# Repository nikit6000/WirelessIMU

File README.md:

# WirelessIMU
A board for wireless motion tracking based on `ESP32-PICO-D4` and `MPU9250`. You also can use `ICM-20948` instead of `MPU9250` but you needs to change LDO at `U1` place to 1.8V one

# Capabilities
* Capture RAW Gyroscope, Accelerometer data to embedded storage
* Control over BLE
* Captured data downloading via Wi-Fi

# Applications
* [iOS Application](https://github.com/tokareva13/WirelessIMU-Control)

# Authors
* [Nikita Tarkhov](https://github.com/nikit6000)
* [Tokareva Irina](https://github.com/tokareva13)

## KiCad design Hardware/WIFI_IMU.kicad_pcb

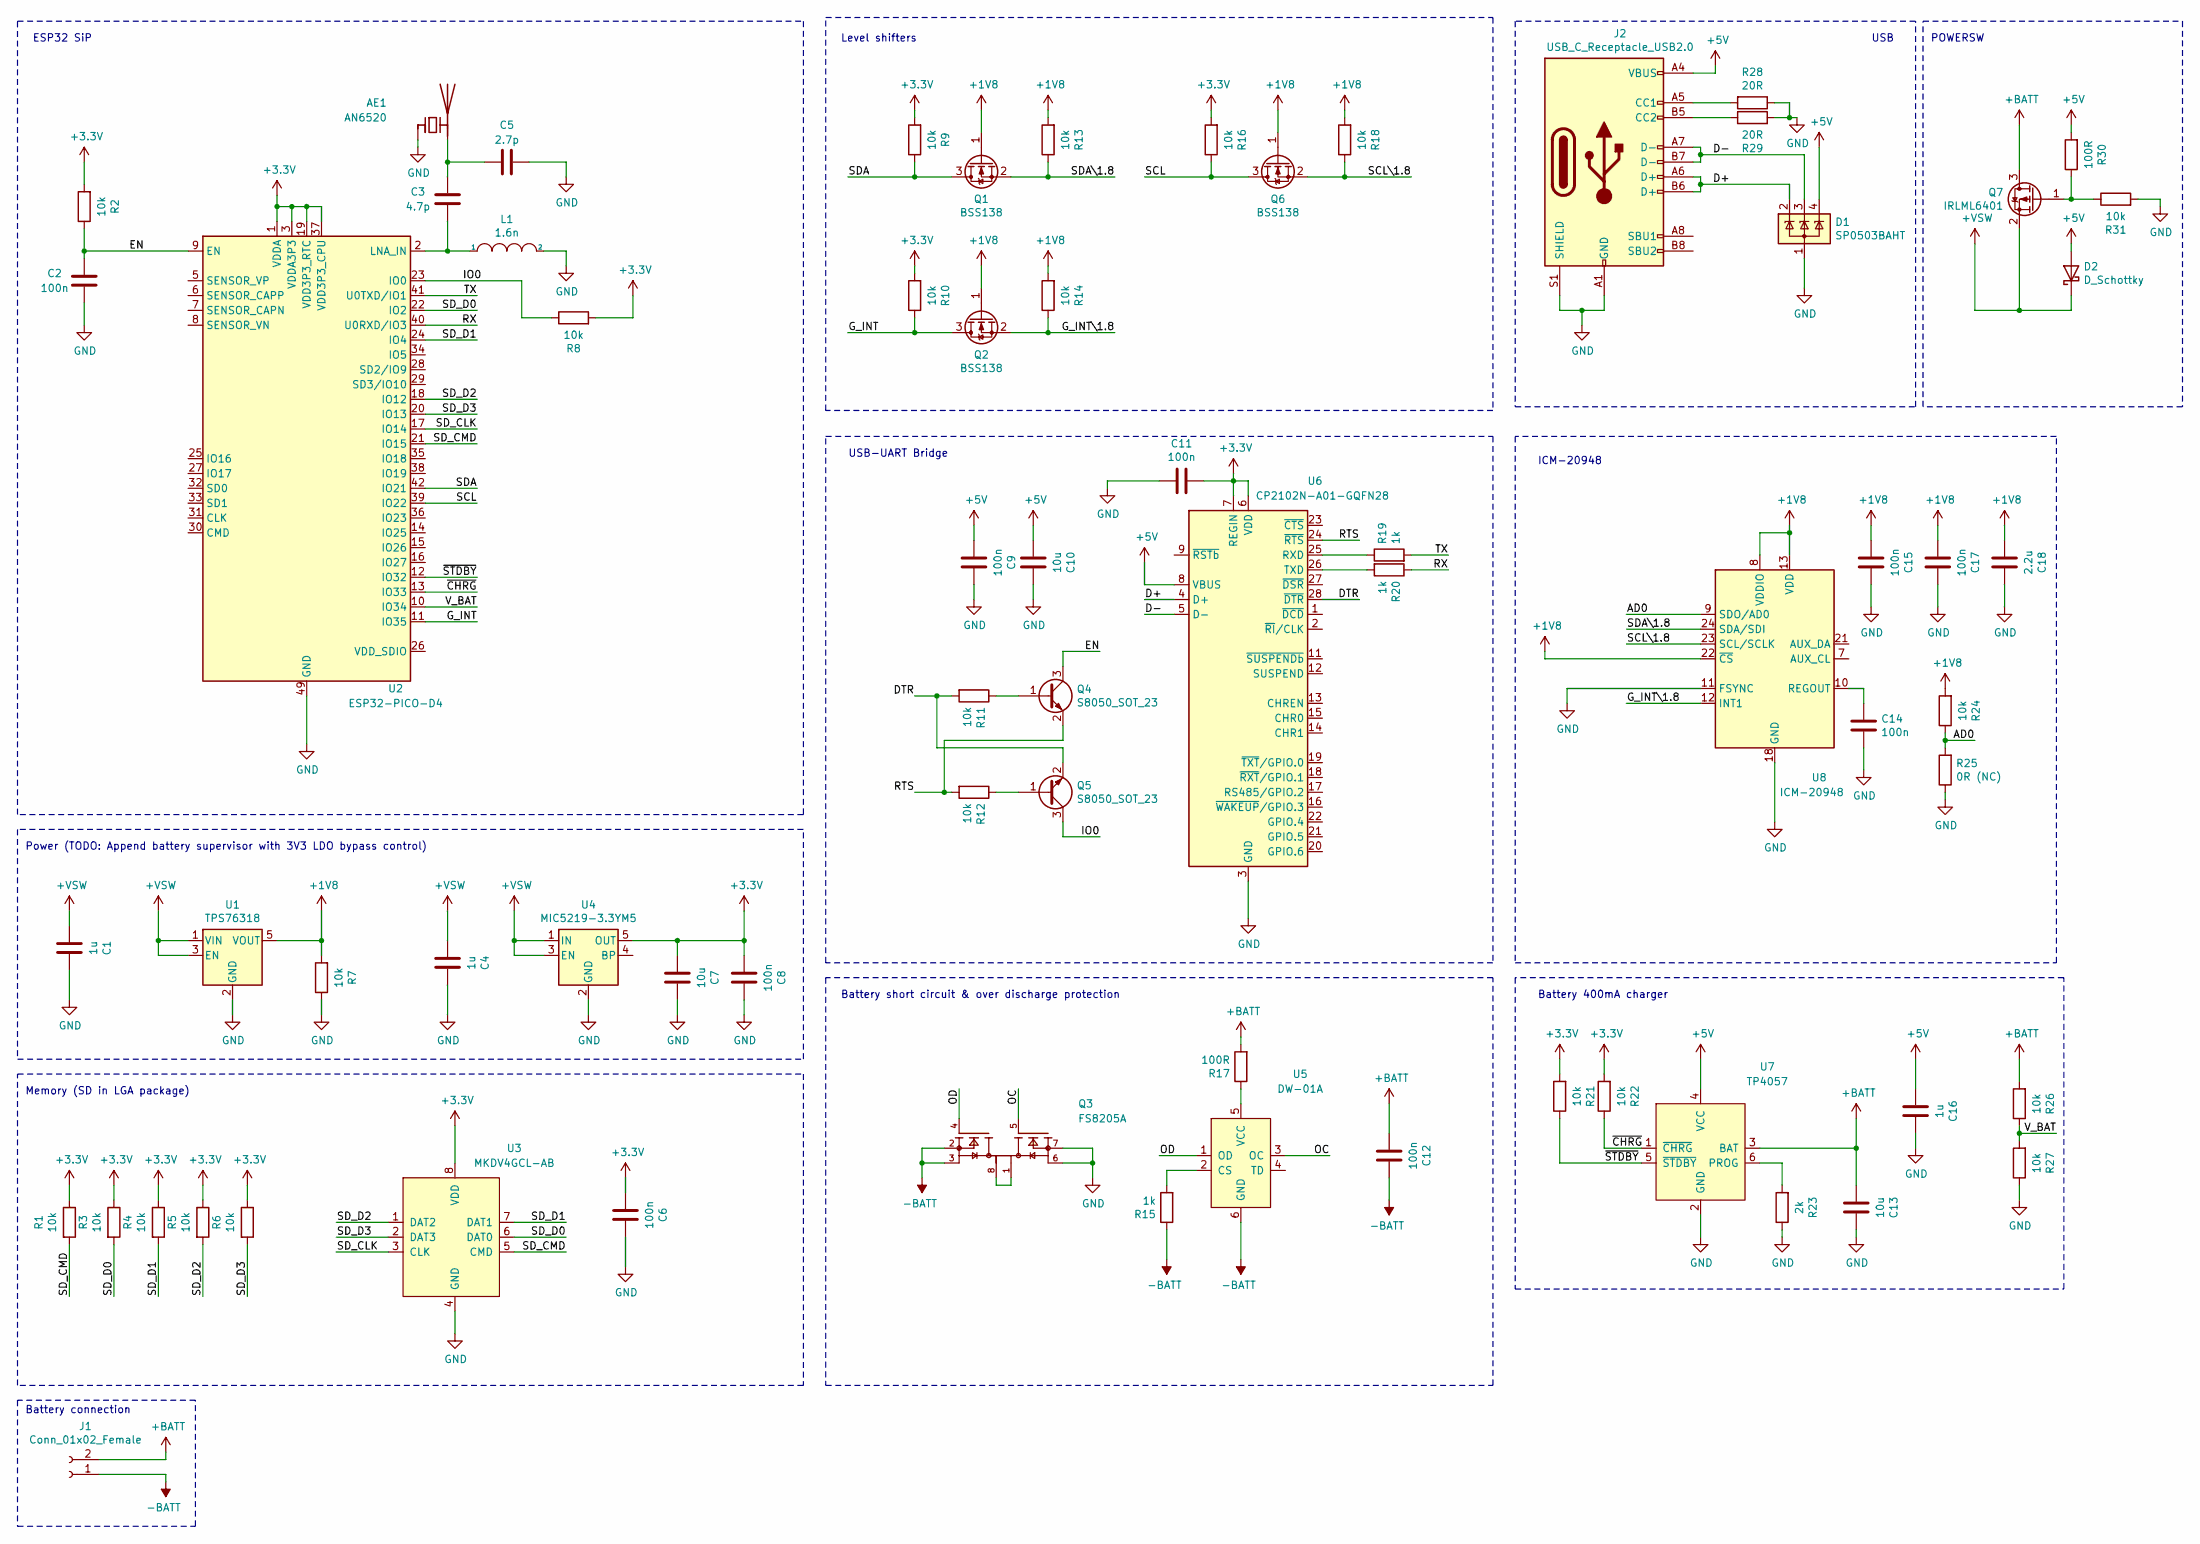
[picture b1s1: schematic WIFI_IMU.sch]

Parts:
AE1: AN6520; CHIP_ANTENNA_AN6520
C1, C4, C16: 1u; C_0402_1005Metric
C2, C6, C8, C9, C11, C12, C14, C15, C17: 100n; C_0402_1005Metric
C3: 4.7p; C_0402_1005Metric
C5: 2.7p; C_0402_1005Metric
C7, C10, C13: 10u; C_0402_1005Metric
C18: 2.2u; C_0402_1005Metric
D1: SP0503BAHT; SOT-143
D2: D_Schottky; D_SOD-323
J1: Conn_01x02_Female; PinHeader_1x02_P1.27mm_Vertical
J2: USB_C_Receptacle_USB2.0; USB_C_Receptacle_HRO_TYPE-C-31-M-12
L1: 1.6n; L_0402_1005Metric
Q1, Q2, Q6: BSS138; SOT-23
Q3: FS8205A; SOP65P640X120-8N; PARTREV 1.7
Q4, Q5: S8050_SOT_23; SOT-23
Q7: IRLML6401; SOT-23
R1, R2, R3, R4, R5, R6, R7, R8, R9, R10, R11, R12, R13, R14, R16, R18, R21, R22, R24, R26, R27, R31: 10k; R_0402_1005Metric
R15, R19, R20: 1k; R_0402_1005Metric
R17, R30: 100R; R_0402_1005Metric
R23: 2k; R_0402_1005Metric
R25: 0R (NC); R_0402_1005Metric
R28, R29: 20R; R_0402_1005Metric
U1: TPS76318; SOT-23-5
U2: ESP32-PICO-D4; QFN-48-1EP_7x7mm_P0.5mm_EP5.3x5.3mm
U3: MKDV4GCL-AB; LGA-8_8x6mm_P1.27
U4: MIC5219-3.3YM5; SOT-23-5
U5: DW-01A; SOT-23-6
U6: CP2102N-A01-GQFN28; QFN-28-1EP_5x5mm_P0.5mm_EP3.35x3.35mm
U7: TP4057; SOT-23-6
U8: ICM-20948; InvenSense_QFN-24_3x3mm_P0.4mm

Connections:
+1V8: C15.2, C17.2, C18.2, Q1.1 (G), Q2.1 (G), Q6.1 (G), R7.2, R13.2, R14.2, R18.2, R24.2, U1.5 (VOUT), U8.8 (VDDIO), U8.13 (VDD), U8.22 (~CS)
+3V3: C6.2, C7.2, C8.2, C11.1, R1.1, R2.2, R3.1, R4.1, R5.1, R6.1, R8.2, R9.2, R10.2, R16.2, R21.2, R22.2, U2.1 (VDDA), U2.3 (VDDA3P3), U2.4 (VDDA3P3), U2.19 (VDD3P3_RTC), U2.37 (VDD3P3_CPU), U2.43 (VDDA), U2.46 (VDDA), U3.8 (VDD), U4.5 (OUT), U6.6 (VDD), U6.7 (REGIN)
+5V: C9.2, C10.2, C16.2, D1.4 (K), D2.2 (A), J2.A4 (VBUS), J2.A9 (VBUS), J2.B4 (VBUS), J2.B9 (VBUS), R30.2, U6.8 (VBUS), U7.4 (VCC)
+BATT: C12.2, C13.2, J1.2, Q7.3 (D), R17.2, R26.2, U7.3 (BAT)
+VSW: C1.2, C4.2, D2.1 (K), Q7.2 (S), U1.1 (VIN), U1.3 (EN), U4.1 (IN), U4.3 (EN)
-BATT: C12.1, J1.1, Q3.2, Q3.3, R15.1, U5.6 (GND)
/AD0: R24.1, R25.2, U8.9 (SDO/AD0)
/D+: D1.2 (K), J2.A6 (D+), J2.B6 (D+), U6.4 (D+)
/D-: D1.3 (K), J2.A7 (D-), J2.B7 (D-), U6.5 (D-)
/DTR: Q5.2 (E), R11.2, U6.28 (~DTR)
/EN: C2.2, Q4.3 (C), R2.1, U2.9 (EN)
/G_INT: Q2.3 (D), R10.1, U2.11 (IO35)
/G_INT\1.8: Q2.2 (S), R14.1, U8.12 (INT1)
/IO0: Q5.3 (C), R8.1, U2.23 (IO0)
/OC: Q3.5, U5.3 (OC)
/OD: Q3.4, U5.1 (OD)
/RTS: Q4.2 (E), R12.2, U6.24 (~RTS)
/RX: R20.1, U2.40 (U0RXD/IO3)
/SCL: Q6.3 (D), R16.1, U2.39 (IO22)
/SCL\1.8: Q6.2 (S), R18.1, U8.23 (SCL/SCLK)
/SDA: Q1.3 (D), R9.1, U2.42 (IO21)
/SDA\1.8: Q1.2 (S), R13.1, U8.24 (SDA/SDI)
/SD_CLK: U2.17 (IO14), U3.3 (CLK)
/SD_CMD: R1.2, U2.21 (IO15), U3.5 (CMD)
/SD_D0: R3.2, U2.22 (IO2), U3.6 (DAT0)
/SD_D1: R4.2, U2.24 (IO4), U3.7 (DAT1)
/SD_D2: R5.2, U2.18 (IO12), U3.1 (DAT2)
/SD_D3: R6.2, U2.20 (IO13), U3.2 (DAT3)
/TX: R19.2, U2.41 (U0TXD/IO1)
/V_BAT: R26.1, R27.2, U2.10 (IO34)
/~CHRG: R22.1, U2.13 (IO33), U7.1 (~CHRG)
/~STDBY: R21.1, U2.12 (IO32), U7.5 (~STDBY)
GND: AE1.2 (FEED), C1.1, C2.1, C4.1, C5.2, C6.1, C7.1, C8.1, C9.1, C10.1, C11.2, C13.1, C14.1, C15.1, C16.1, C17.1, C18.1, D1.1 (A), J2.A1 (GND), J2.A12 (GND), J2.B1 (GND), J2.B12 (GND), J2.S1 (SHIELD), L1.2, Q3.6, Q3.7, R7.1, R23.1, R25.1, R27.1, R28.1, R29.2, R31.2, U1.2 (GND), U2.49 (GND), U3.4 (GND), U4.2 (GND), U6.3 (GND), U6.29 (GND), U7.2 (GND), U8.11 (FSYNC), U8.18 (GND), U8.20 (GND)
unnamed: AE1.1 (PCB_Trace), C3.2, C5.1
unnamed: C3.1, L1.1, U2.2 (LNA_IN)
unnamed: C14.2, U8.10 (REGOUT)
unnamed: J2.A5 (CC1), R28.2
unnamed: J2.B5 (CC2), R29.1
unnamed: Q3.1, Q3.8
unnamed: Q4.1 (B), R11.1
unnamed: Q5.1 (B), R12.1
unnamed: Q7.1 (G), R30.1, R31.1
unnamed: R15.2, U5.2 (CS)
unnamed: R17.1, U5.5 (VCC)
unnamed: R19.1, U6.25 (RXD)
unnamed: R20.2, U6.26 (TXD)
unnamed: R23.2, U7.6 (PROG)

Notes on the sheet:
ESP32 SiP
USB
USB-UART Bridge
ICM-20948
Level shifters
Power (TODO: Append battery supervisor with 3V3 LDO bypass control)
Memory (SD in LGA package)
Battery short circuit & over discharge protection
Battery 400mA charger
Battery connection
POWERSW

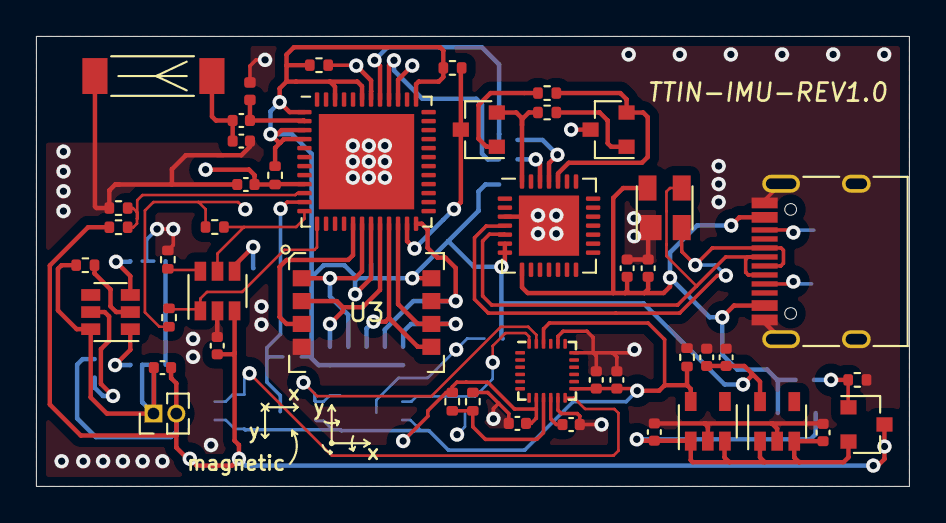
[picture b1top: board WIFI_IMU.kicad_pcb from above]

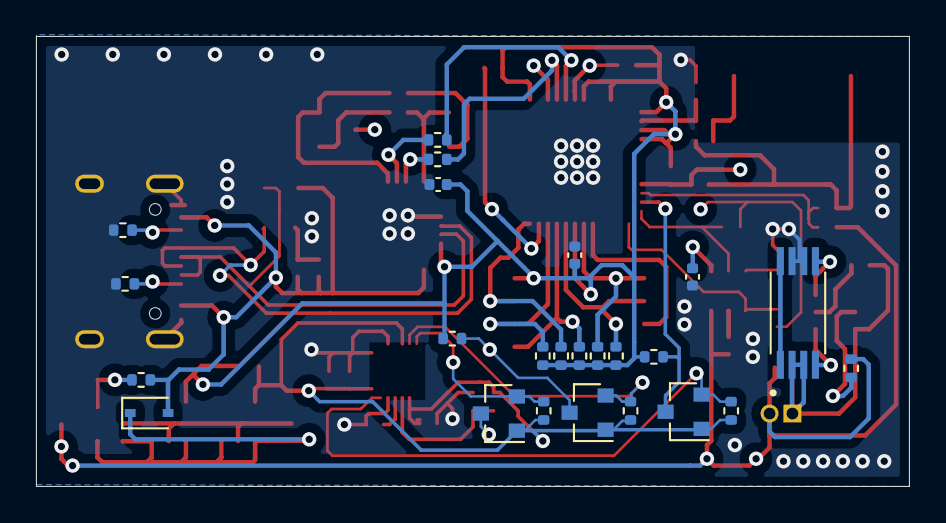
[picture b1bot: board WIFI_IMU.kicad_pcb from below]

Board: 4 copper layers, 48.5 x 25.0 mm, 70 parts (24 on the bottom side), 47 nets.

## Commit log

2022-10-06 Initail commit
2022-10-06 Add PCB image
